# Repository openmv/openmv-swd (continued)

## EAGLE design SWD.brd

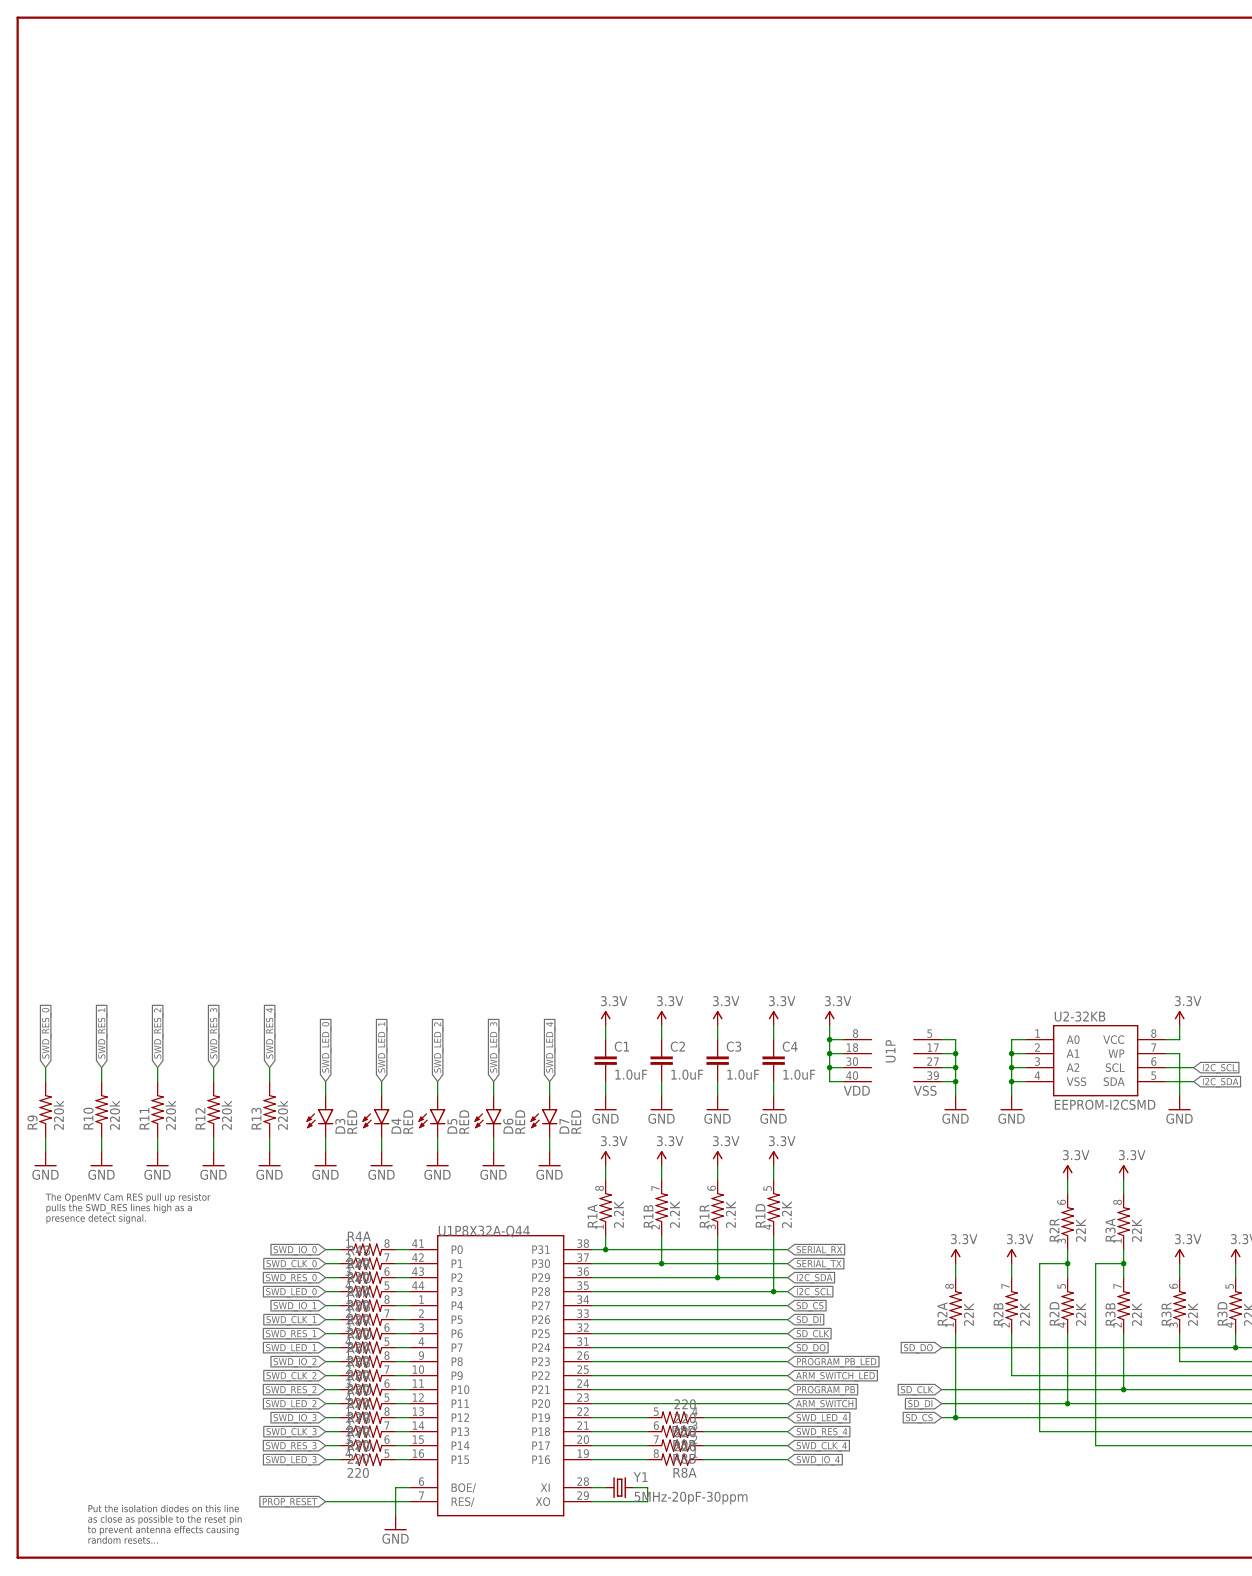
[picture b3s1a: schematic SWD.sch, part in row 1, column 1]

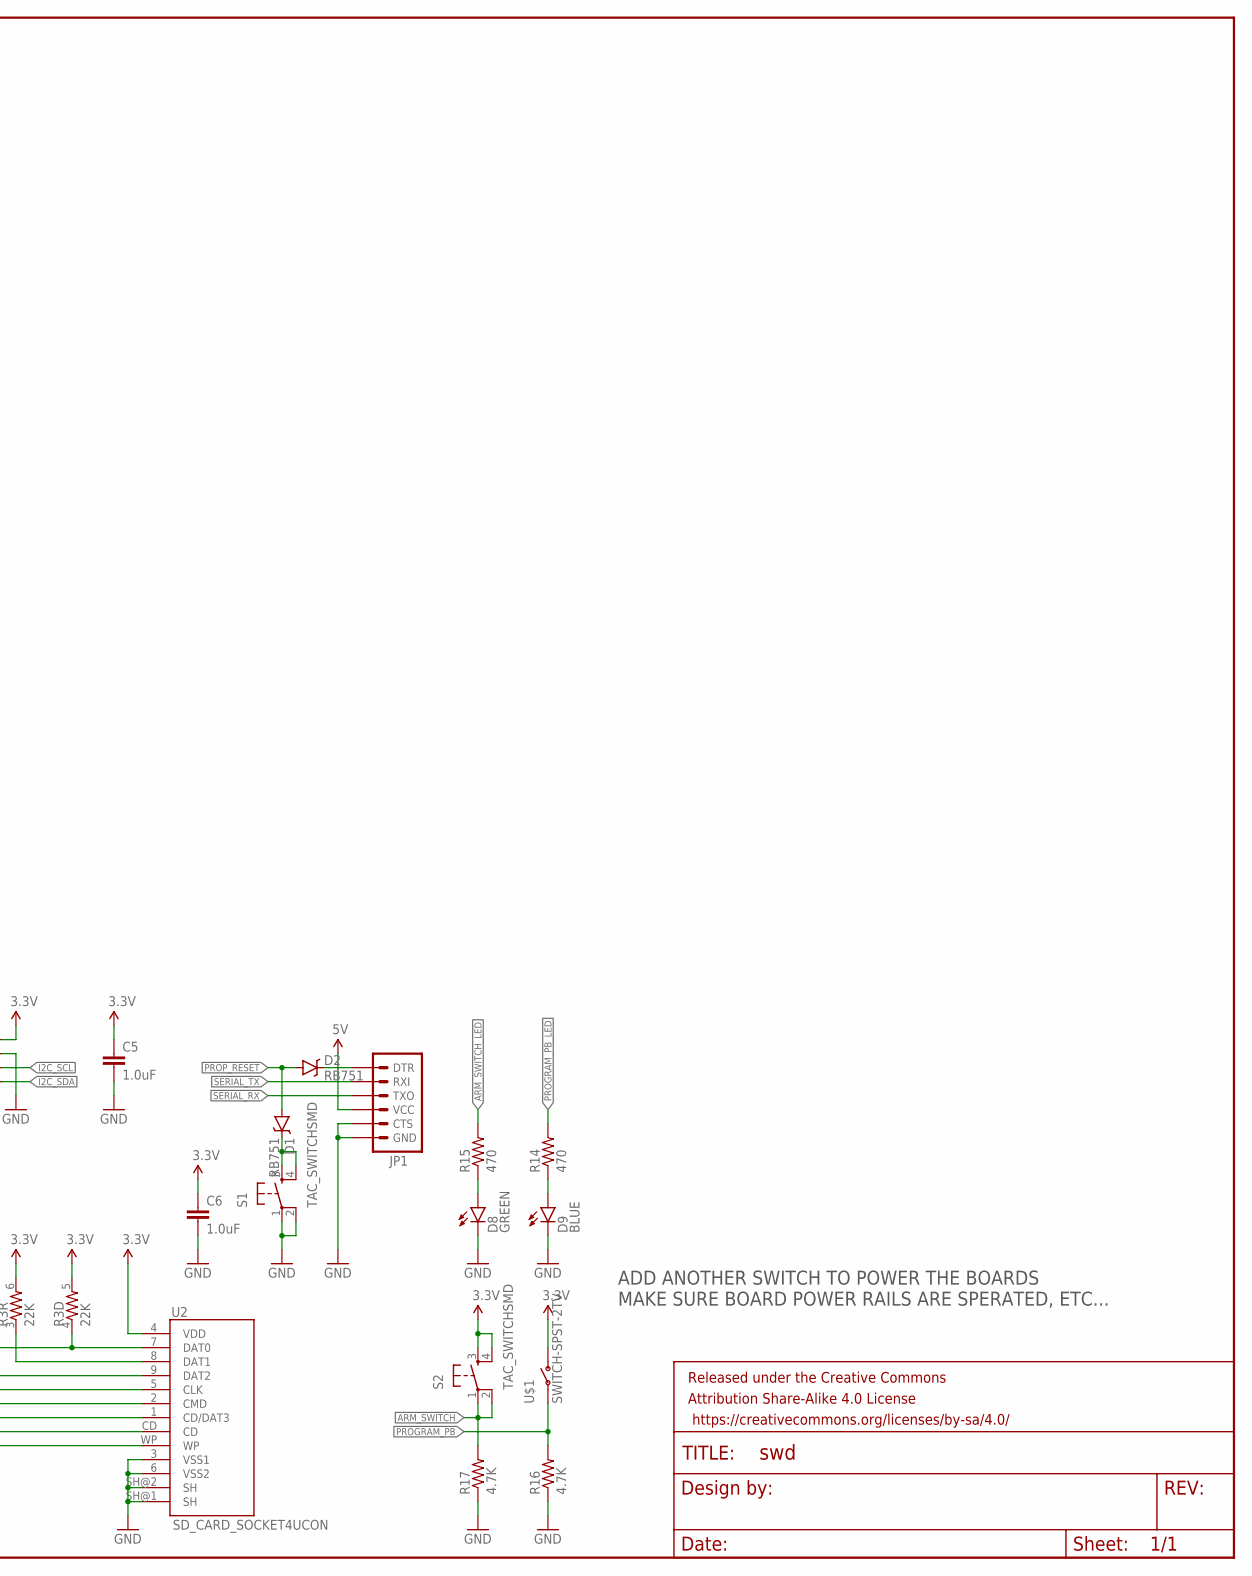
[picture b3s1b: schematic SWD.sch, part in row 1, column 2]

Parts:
C1, C2, C3, C4, C5, C6: 1.0uF; 0402-CAP
D1, D2: RB751; SOD-523
D3, D4, D5, D6, D7: RED; LED-0603
D8: GREEN; LED-0603
D9: BLUE; LED-0603
FRAME1: FRAME-LEDGER; CREATIVE_COMMONS
JP1: ARDUINO_SERIAL_PROGRAMPTH; 1X06
R1: 2.2K; 0603-ARV
R2, R3: 22K; 0603-ARV
R4, R5, R6, R7, R8: 220; 0603-ARV
R9, R10, R11, R12, R13: 220k; 0603-RES
R14, R15: 470; 0603-RES
R16, R17: 4.7K; 0603-RES
S1, S2: TAC_SWITCHSMD; TACTILE-SWITCH-SMD
U1: P8X32A-Q44
U2: SD_CARD_SOCKET4UCON; SDCARD_4UCONN
U2-32KB: EEPROM-I2CSMD; SO08
U$1: SWITCH-SPST-2TV; SWITCH-SPST-VERTICAL
Y1: 5MHz-20pF-30ppm; HC49UP

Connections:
3.3V: C1.1, C2.1, C3.1, C4.1, C5.1, C6.1, R1.5 (2), R1.6 (2), R1.7 (2), R1.8 (2), R2.6 (2), R2.7 (2), R2.8 (2), R3.5 (2), R3.6 (2), R3.8 (2), S2.3, S2.4, U1.8 (VDD), U1.18 (VDD), U1.30 (VDD), U1.40 (VDD), U2.4 (VDD), U2-32KB.8 (VCC), U$1.1 (O)
5V: JP1.4 (VCC)
ARM_SWITCH: R17.2, S2.1, S2.2, U1.23 (P20)
ARM_SWITCH_LED: R15.2, U1.25 (P22)
GND: C1.2, C2.2, C3.2, C4.2, C5.2, C6.2, D3.C, D4.C, D5.C, D6.C, D7.C, D8.C, D9.C, JP1.5 (CTS), JP1.6 (GND), R9.1, R10.1, R11.1, R12.1, R13.1, R16.1, R17.1, S1.1, S1.2, U1.5 (VSS), U1.6 (BOE/), U1.17 (VSS), U1.27 (VSS), U1.39 (VSS), U2.3 (VSS1), U2.6 (VSS2), U2.SH@1 (SH), U2.SH@2 (SH), U2-32KB.1 (A0), U2-32KB.2 (A1), U2-32KB.3 (A2), U2-32KB.4 (VSS), U2-32KB.7 (WP)
I2C_SCL: R1.4 (1), U1.35 (P28), U2-32KB.6 (SCL)
I2C_SDA: R1.3 (1), U1.36 (P29), U2-32KB.5 (SDA)
unnamed: R4.8 (2), U1.41 (P0)
unnamed: R4.7 (2), U1.42 (P1)
unnamed: U1.28 (XI), Y1.1
unnamed: U1.29 (XO), Y1.2
unnamed: D8.A, R15.1
unnamed: R4.6 (2), U1.43 (P2)
unnamed: R4.5 (2), U1.44 (P3)
unnamed: D1.C, S1.3, S1.4
unnamed: R5.8 (2), U1.1 (P4)
unnamed: R5.7 (2), U1.2 (P5)
unnamed: R5.6 (2), U1.3 (P6)
unnamed: R5.5 (2), U1.4 (P7)
unnamed: R6.8 (2), U1.9 (P8)
unnamed: R3.1, R3.7 (2), U2.WP
unnamed: R6.7 (2), U1.10 (P9)
unnamed: R2.3 (1), R2.5 (2), U2.CD
unnamed: R6.6 (2), U1.11 (P10)
unnamed: R6.5 (2), U1.12 (P11)
unnamed: R7.8 (2), U1.13 (P12)
unnamed: R7.7 (2), U1.14 (P13)
unnamed: R7.6 (2), U1.15 (P14)
unnamed: R7.5 (2), U1.16 (P15)
unnamed: R8.5 (2), U1.22 (P19)
unnamed: R8.6 (2), U1.21 (P18)
unnamed: R8.7 (2), U1.20 (P17)
unnamed: R8.8 (2), U1.19 (P16)
unnamed: D2.C, JP1.1 (DTR)
unnamed: D9.A, R14.1
PROGRAM_PB: R16.2, U1.24 (P21), U$1.2
PROGRAM_PB_LED: R14.2, U1.26 (P23)
PROP_RESET: D1.A, D2.A, U1.7 (RES/)
SD_CLK: R3.2 (1), U1.32 (P25), U2.5 (CLK)
SD_CS: R2.1, R3.3 (1), U1.34 (P27), U2.1 (CD/DAT3), U2.8 (DAT1)
SD_DI: R2.4 (1), U1.33 (P26), U2.2 (CMD)
SD_DO: R2.2 (1), R3.4 (1), U1.31 (P24), U2.7 (DAT0), U2.9 (DAT2)
SERIAL_RX: JP1.3 (TXO), R1.1, U1.38 (P31)
SERIAL_TX: JP1.2 (RXI), R1.2 (1), U1.37 (P30)
SWD_CLK_0: R4.2 (1)
SWD_CLK_1: R5.2 (1)
SWD_CLK_2: R6.2 (1)
SWD_CLK_3: R7.2 (1)
SWD_CLK_4: R8.2 (1)
SWD_IO_0: R4.1
SWD_IO_1: R5.1
SWD_IO_2: R6.1
SWD_IO_3: R7.1
SWD_IO_4: R8.1
SWD_LED_0: D3.A, R4.4 (1)
SWD_LED_1: D4.A, R5.4 (1)
SWD_LED_2: D5.A, R6.4 (1)
SWD_LED_3: D6.A, R7.4 (1)
SWD_LED_4: D7.A, R8.4 (1)
SWD_RES_0: R4.3 (1), R9.2
SWD_RES_1: R5.3 (1), R10.2
SWD_RES_2: R6.3 (1), R11.2
SWD_RES_3: R7.3 (1), R12.2
SWD_RES_4: R8.3 (1), R13.2

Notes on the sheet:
The OpenMV Cam RES pull up resistor pulls the SWD_RES lines high as a presence detect signal.
Put the isolation diodes on this line as close as possible to the reset pin to prevent antenna effects causing random resets...
ADD ANOTHER SWITCH TO POWER THE BOARDS MAKE SURE BOARD POWER RAILS ARE SPERATED, ETC...

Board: 2 copper layers, 41 parts (0 on the bottom side), 53 nets, no tracks yet.

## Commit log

2015-05-22 Added files
2015-05-31 Working on firmware...
2015-06-03 Almost done
2015-06-04 Ready to test
2015-06-13 Firmware done...
2015-06-14 Made faster
2015-06-15 Add SWD jig
2015-06-20 Generated firmware
2015-06-20 updated asm
2015-06-20 try again
2015-06-25 * Update jig (see details)
    * Make SWD resistors 100 ohms (RN5-RN2)
    * Remove D1 (not really needed).
    * Add propeller reset circuit.
    * Change all pull-up resistors to 10K.
    * Add more silkscreen labels (power switch, power LED, 5V input).
    * Use different colors for the power LED, program LED, and board LEDs.
2015-06-27 Replace common parts with MF parts
2015-09-08 Fixed path
2017-01-30 Update SWD
2017-01-30 Add binary
2017-02-01 SWD app initial commit
2017-02-02 Lots more work done
2017-02-04 SWD app done
2017-02-04 Editing script name
2017-02-06 Added 10 second beep.
2017-02-15 Release
2017-02-19 Fixed latin1 stuff
2017-02-22 Added large timeout between turning a row on and off
2017-02-22 Add RTS reset.
2017-02-22 RTS reset.
2017-02-23 Fixed stuff up
2017-03-13 Speed up SWD programmer
2017-03-13 Seems to work
2017-03-13 Alternative SWD code
2017-04-04 Fixed waiting
2017-04-24 Fixed spelling
2017-04-30 Fixed wire errors
2017-05-04 Added enable buttons
2017-07-23 Serial port fixes
2017-07-23 Updated media
2017-07-29 New media
2018-01-20 Update firmware version
2018-02-07 Update media
2018-02-18 Update repos
2018-12-02 Update the jig firmware to handle the H7
2018-12-02 Update firmware binaries
2018-12-02 Update binaries
2018-12-02 Update version
2020-10-20 Remove flash verification
2020-10-20 Update to work with the Portenta
